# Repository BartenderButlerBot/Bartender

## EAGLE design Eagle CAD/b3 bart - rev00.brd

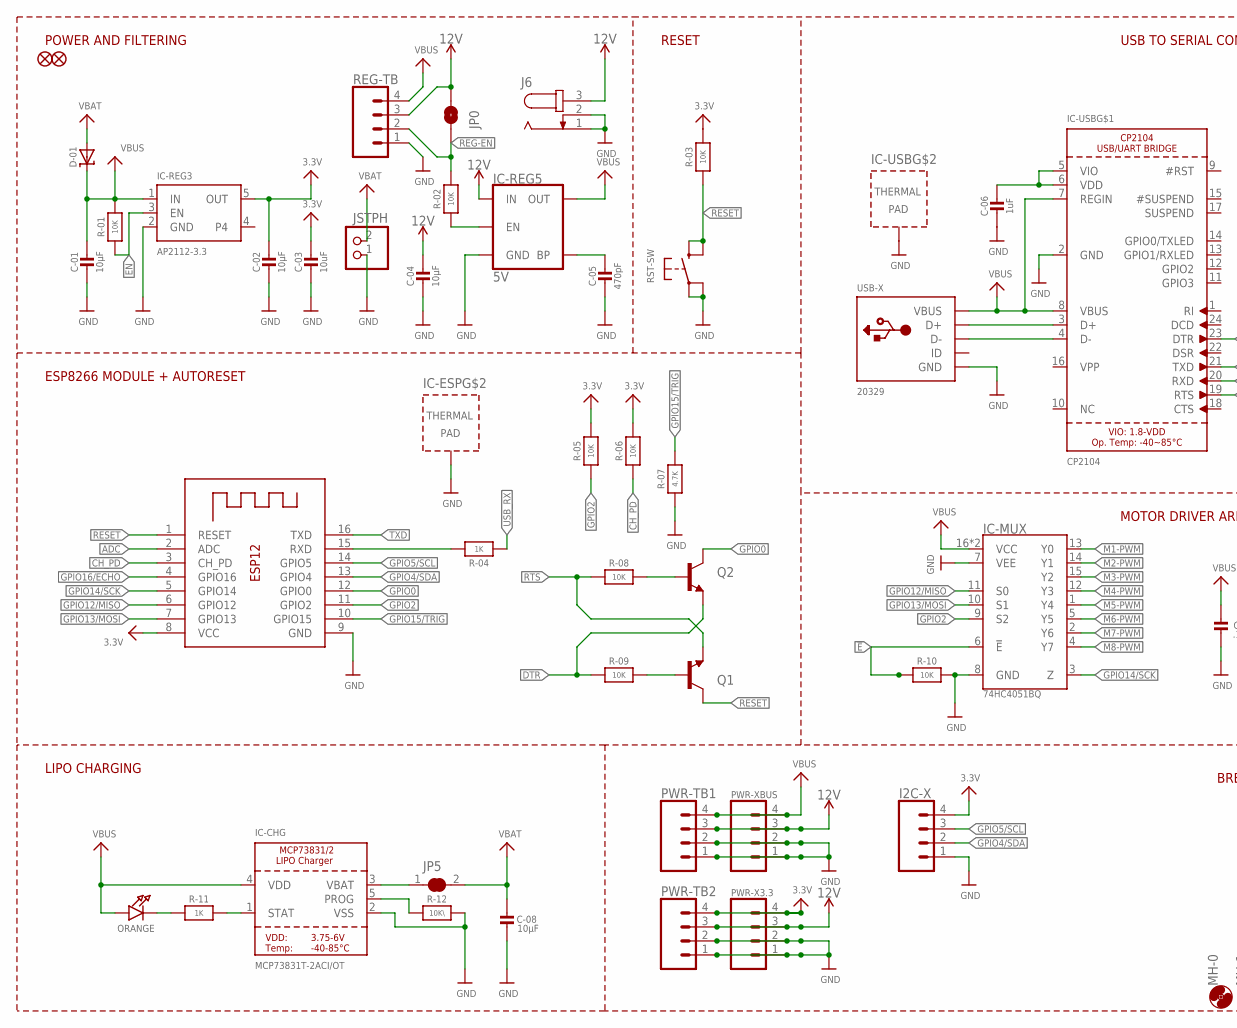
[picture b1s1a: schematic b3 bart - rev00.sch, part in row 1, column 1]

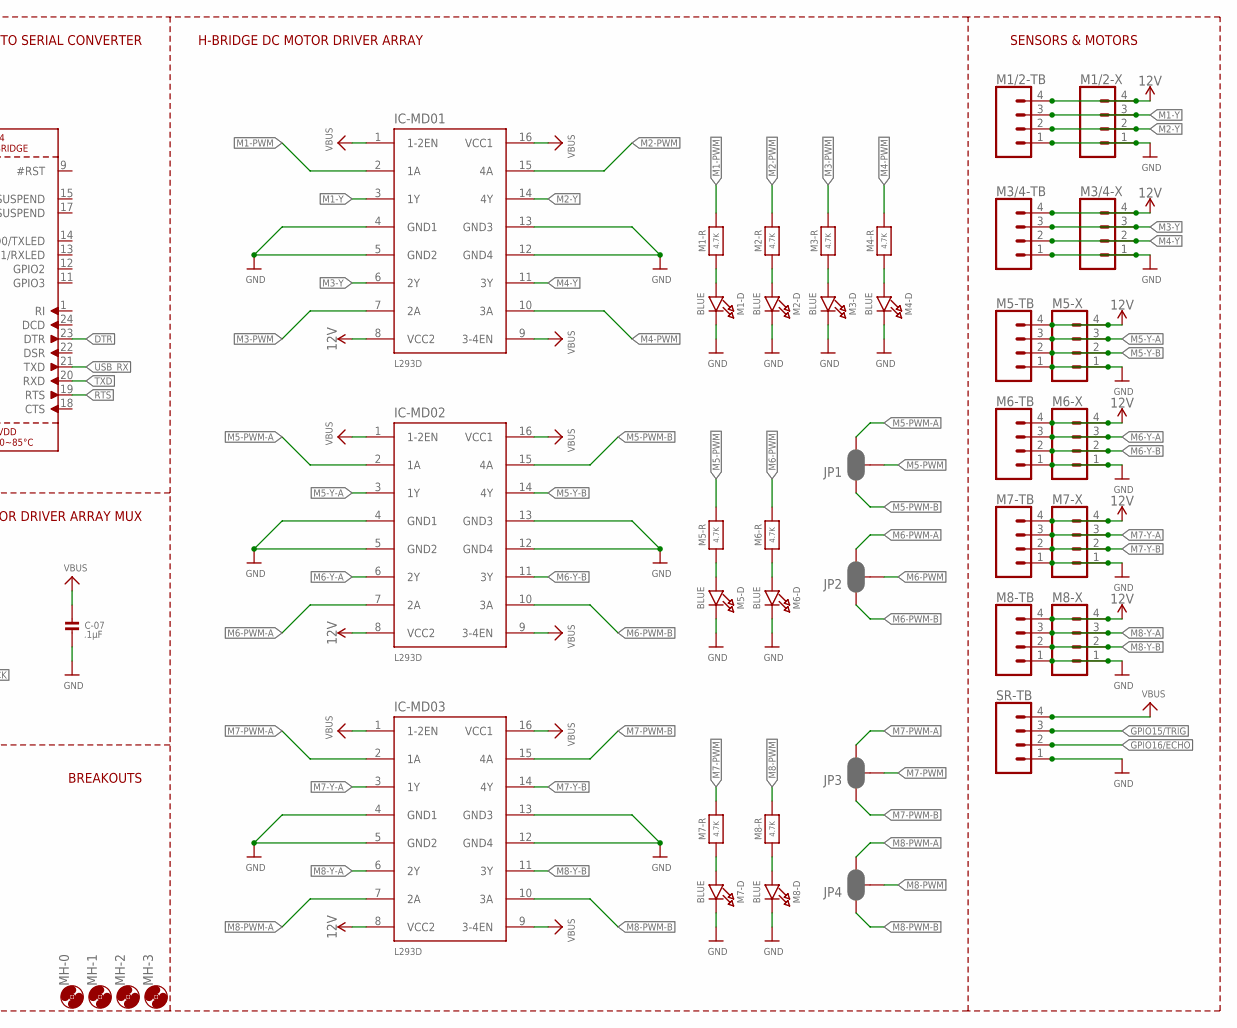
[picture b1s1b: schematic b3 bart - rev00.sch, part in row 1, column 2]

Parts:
C-01, C-02, C-04, C-08: 10µF; 0805-NO
C-03: 10uF; 0805-NO
C-05: 470pF; 0805-NO
C-06: 1uF; 0603-NO@1
C-07: .1µF; 0805-NO
CHG-D: ORANGE; CHIPLED_0805_NOOUTLINE
D-01: MBR120; SOD-123
FD1, FD2: FIDUCIAL1X2; FIDUCIAL-1X2
I2C-X: CONN_04LONGPADS; 1X04_LONGPADS
IC-CHG: MCP73831T-2ACI/OT; SOT23-5
IC-ESP: ESP-12; ESP-12S
IC-MD01, IC-MD02, IC-MD03: L293D; DIL16
IC-MUX: 74HC4051BQ; DHVQFN-16-2.5X3.5MM
IC-REG3: AP2112-3.3; SOT23-5
IC-REG5: 5V; SOT23-5
IC-USB: CP2104; QFN24_4MM_SMSC
J6: JACK-PLUG1; SPC4078
JP0: JUMPER-SMT_2_NO_SILK; SMT-JUMPER_2_NO_SILK
JP1, JP2, JP3, JP4: JUMPER-SMT_3_2-NC_PASTE_SILK; SMT-JUMPER_3_2-NC_PASTE_SILK
JP5: SOLDERJUMPER_CLOSED; SOLDERJUMPER_CLOSEDWIRE
M1-D, M2-D, M3-D, M4-D, M5-D, M6-D, M7-D, M8-D: BLUE; CHIPLED_0805_NOOUTLINE
M1-R, M2-R, M3-R, M4-R, M5-R, M6-R, M7-R, M8-R: 4.7K; 0603-NO
M1/2-TB, M3/4-TB, M5-TB, M6-TB, M7-TB, M8-TB: CONN_04SCREW; SCREWTERMINAL-3.5MM-4
M1/2-X, M3/4-X, M5-X, M6-X, M7-X, M8-X: CONN_04LONGPADS; 1X04_LONGPADS
MH-0, MH-1, MH-2, MH-3: MOUNT-HOLE3.0; 3,0
PWR-TB1, PWR-TB2: CONN_04SCREW; SCREWTERMINAL-3.5MM-4
PWR-X3.3: CONN_04LONGPADS; 1X04_LONGPADS
PWR-XBUS: CONN_04LONGPADS; 1X04_LONGPADS
Q1, Q2: mmbt2222; SOT23-3
R-01, R-02, R-03, R-05, R-06, R-08, R-09, R-10: 10K; 0603-NO
R-04: 1K; _0603MP
R-07: 4.7K; 0603-NO
R-11: 1K; 0603-NO
R-12: 10K\; 0603-NO
REG-TB: CONN_04SCREW; SCREWTERMINAL-3.5MM-4
RST-SW: KMR2; BTN_KMR2_4.6X2.8
SR-TB: CONN_04SCREW; SCREWTERMINAL-3.5MM-4
USB-X: 20329; 4UCONN_20329_V2
X1: JSTPH; JSTPH2

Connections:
3.3V: C-02.1, C-03.1, I2C-X.4, IC-ESP.8 (VCC), IC-REG3.5 (OUT), PWR-TB2.4, PWR-X3.3.4, R-03.2, R-05.2, R-06.2
12V: C-04.1, IC-MD01.8 (VCC2), IC-MD02.8 (VCC2), IC-MD03.8 (VCC2), IC-REG5.1 (IN), J6.3, JP0.2, M1/2-TB.4, M1/2-X.4, M3/4-TB.4, M3/4-X.4, M5-TB.4, M5-X.4, M6-TB.4, M6-X.4, M7-TB.4, M7-X.4, M8-TB.4, M8-X.4, PWR-TB1.3, PWR-TB2.3, PWR-X3.3.3, PWR-XBUS.3, REG-TB.3
!E!: IC-MUX.6 (!E!), R-10.1
ADC: IC-ESP.2 (ADC)
CH_PD: IC-ESP.3 (CH_PD), R-06.1
D+: IC-USB.3 (D+), USB-X.D+
D-: IC-USB.4 (D-), USB-X.D-
DTR: IC-USB.23 (DTR), Q2.2 (E), R-09.1
EN: IC-REG3.3 (EN), R-01.1
GND: C-01.2, C-02.2, C-03.2, C-04.2, C-05.2, C-06.2, C-07.2, C-08.2, I2C-X.1, IC-CHG.2 (VSS), IC-ESP.9 (GND), IC-ESP.P$1 (TP), IC-MD01.4 (GND1), IC-MD01.5 (GND2), IC-MD01.12 (GND4), IC-MD01.13 (GND3), IC-MD02.4 (GND1), IC-MD02.5 (GND2), IC-MD02.12 (GND4), IC-MD02.13 (GND3), IC-MD03.4 (GND1), IC-MD03.5 (GND2), IC-MD03.12 (GND4), IC-MD03.13 (GND3), IC-MUX.7 (VEE), IC-MUX.8 (GND), IC-REG3.2 (GND), IC-REG5.2 (GND), IC-USB.2 (GND), IC-USB.THERM (TP), J6.1, J6.2, M1-D.C, M1/2-TB.1, M1/2-X.1, M2-D.C, M3-D.C, M3/4-TB.1, M3/4-X.1, M4-D.C, M5-D.C, M5-TB.1, M5-X.1, M6-D.C, M6-TB.1, M6-X.1, M7-D.C, M7-TB.1, M7-X.1, M8-D.C, M8-TB.1, M8-X.1, PWR-TB1.1, PWR-TB1.2, PWR-TB2.1, PWR-TB2.2, PWR-X3.3.1, PWR-X3.3.2, PWR-XBUS.1, PWR-XBUS.2, R-07.1, R-10.2, R-12.2, REG-TB.1, RST-SW.A, RST-SW.A' (P1), SR-TB.1, USB-X.BASE@1 (GND), USB-X.BASE@2 (GND), USB-X.GND, USB-X.SPRT@1 (GND), USB-X.SPRT@2 (GND), USB-X.SPRT@3 (GND), USB-X.SPRT@4 (GND), X1.1
GPIO0: IC-ESP.12 (GPIO0), Q2.3 (C)
GPIO2: IC-ESP.11 (GPIO2), IC-MUX.9 (S2), R-05.1
GPIO4/SDA: I2C-X.2, IC-ESP.13 (GPIO4)
GPIO5/SCL: I2C-X.3, IC-ESP.14 (GPIO5)
GPIO12/MISO: IC-ESP.6 (GPIO12), IC-MUX.11 (S0)
GPIO13/MOSI: IC-ESP.7 (GPIO13), IC-MUX.10 (S1)
GPIO14/SCK: IC-ESP.5 (GPIO14), IC-MUX.3 (Z)
GPIO15/TRIG: IC-ESP.10 (GPIO15), R-07.2, SR-TB.3
GPIO16/ECHO: IC-ESP.4 (GPIO16), SR-TB.2
M1-PWM: IC-MD01.2 (1A), IC-MUX.13 (Y0), M1-R.2
M1-Y: IC-MD01.3 (1Y), M1/2-TB.3, M1/2-X.3
M2-PWM: IC-MD01.15 (4A), IC-MUX.14 (Y1), M2-R.2
M2-Y: IC-MD01.14 (4Y), M1/2-TB.2, M1/2-X.2
M3-PWM: IC-MD01.7 (2A), IC-MUX.15 (Y2), M3-R.2
M3-Y: IC-MD01.6 (2Y), M3/4-TB.3, M3/4-X.3
M4-PWM: IC-MD01.10 (3A), IC-MUX.12 (Y3), M4-R.2
M4-Y: IC-MD01.11 (3Y), M3/4-TB.2, M3/4-X.2
M5-PWM: IC-MUX.1 (Y4), JP1.2, M5-R.2
M5-PWM-A: IC-MD02.2 (1A), JP1.3
M5-PWM-B: IC-MD02.15 (4A), JP1.1
M5-Y-A: IC-MD02.3 (1Y), M5-TB.3, M5-X.3
M5-Y-B: IC-MD02.14 (4Y), M5-TB.2, M5-X.2
M6-PWM: IC-MUX.5 (Y5), JP2.2, M6-R.2
M6-PWM-A: IC-MD02.7 (2A), JP2.3
M6-PWM-B: IC-MD02.10 (3A), JP2.1
M6-Y-A: IC-MD02.6 (2Y), M6-TB.3, M6-X.3
M6-Y-B: IC-MD02.11 (3Y), M6-TB.2, M6-X.2
M7-PWM: IC-MUX.2 (Y6), JP3.2, M7-R.2
M7-PWM-A: IC-MD03.2 (1A), JP3.3
M7-PWM-B: IC-MD03.15 (4A), JP3.1
M7-Y-A: IC-MD03.3 (1Y), M7-TB.3, M7-X.3
M7-Y-B: IC-MD03.14 (4Y), M7-TB.2, M7-X.2
M8-PWM: IC-MUX.4 (Y7), JP4.2, M8-R.2
M8-PWM-A: IC-MD03.7 (2A), JP4.3
M8-PWM-B: IC-MD03.10 (3A), JP4.1
M8-Y-A: IC-MD03.6 (2Y), M8-TB.3, M8-X.3
M8-Y-B: IC-MD03.11 (3Y), M8-TB.2, M8-X.2
unnamed: CHG-D.C, R-11.1
unnamed: M5-D.A, M5-R.1
unnamed: IC-CHG.1 (STAT), R-11.2
unnamed: IC-CHG.5 (PROG), R-12.1
unnamed: M6-D.A, M6-R.1
unnamed: M1-D.A, M1-R.1
unnamed: IC-CHG.3 (VBAT), JP5.1
unnamed: C-06.1, IC-USB.5 (VIO), IC-USB.6 (VDD)
unnamed: M2-D.A, M2-R.1
unnamed: IC-REG5.3 (EN), R-02.1
unnamed: M7-D.A, M7-R.1
unnamed: Q1.1 (B), R-09.2
unnamed: Q2.1 (B), R-08.2
unnamed: M8-D.A, M8-R.1
unnamed: M3-D.A, M3-R.1
unnamed: M4-D.A, M4-R.1
unnamed: C-05.1, IC-REG5.4 (BP)
REG-EN: JP0.1, R-02.2, REG-TB.2
RESET: IC-ESP.1 (RESET), Q1.3 (C), R-03.1, RST-SW.B (S), RST-SW.B' (S1)
RTS: IC-USB.19 (RTS), Q1.2 (E), R-08.1
RXD: IC-ESP.15 (RXD), R-04.2
TXD: IC-ESP.16 (TXD), IC-USB.20 (RXD)
USB_RX: IC-USB.21 (TXD), R-04.1
VBAT: C-08.1, D-01.A, JP5.2, X1.2
VBUS: C-01.1, C-07.1, CHG-D.A, D-01.C, IC-CHG.4 (VDD), IC-MD01.1 (1-2EN), IC-MD01.9 (3-4EN), IC-MD01.16 (VCC1), IC-MD02.1 (1-2EN), IC-MD02.9 (3-4EN), IC-MD02.16 (VCC1), IC-MD03.1 (1-2EN), IC-MD03.9 (3-4EN), IC-MD03.16 (VCC1), IC-MUX.16 (VCC), IC-MUX.EP (VCC), IC-REG3.1 (IN), IC-REG5.5 (OUT), IC-USB.7 (REGIN), IC-USB.8 (VBUS), PWR-TB1.4, PWR-XBUS.4, R-01.2, REG-TB.4, SR-TB.4, USB-X.VBUS

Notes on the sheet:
POWER AND FILTERING
RESET
LIPO CHARGING
ESP8266 MODULE + AUTORESET
H-BRIDGE DC MOTOR DRIVER ARRAY
USB TO SERIAL CONVERTER
MOTOR DRIVER ARRAY MUX
BREAKOUTS
SENSORS & MOTORS

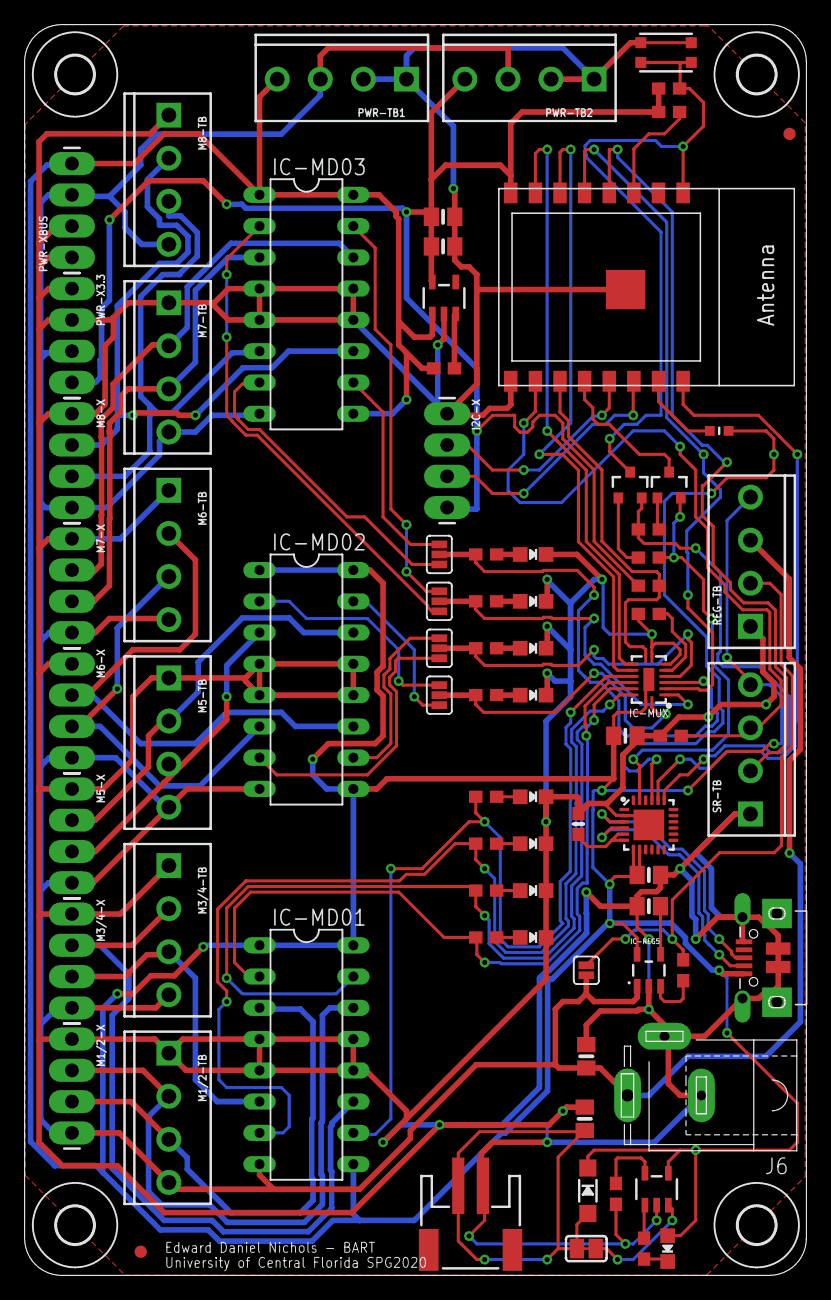
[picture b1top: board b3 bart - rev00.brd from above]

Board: 2 copper layers, 63.5 x 101.6 mm, 84 parts (0 on the bottom side), 71 nets.

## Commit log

2020-01-16 init MQTT functionality for ESP8266
2020-03-12 CAD, firmware blitz
2020-03-20 Eagle PCB files, as submitted for quotation
2020-03-20 bartender demo
2020-04-02 rev4, mqtt subscribe & other bartender functions
2020-04-06 i'm doing my best dammit
2020-04-07 progress anyway
2020-04-07 mqtt died again, no idea why
2020-04-10 switched libraries to pubsub and it works
2020-04-10 parsing incoming messages, almost auto pumps
2020-04-11 it works ^_^
2020-04-12 bartender is done, troubleshooting & testing enabled
2020-04-13 fine tuning. demo vid success!

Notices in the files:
parts and their libraries:
microbuilder: This work is placed in the public domain, and may be freely used for commercial and non-commercial work with the following conditions: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
SparkFun: Licensing: CC v3.0 Share-Alike You are welcome to use this library for commercial purposes.
